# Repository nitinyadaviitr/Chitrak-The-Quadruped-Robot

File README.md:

MaRS_Kitty
Walking Quadruped Robot Kitty is a Quadruped that we are building under Models and Robotics Section, IIT Roorkee. 
This four legged walking robot will mimic the gait cycle of a cat with a soul purpose of providing help in natural calamities where 
normal robots find it difficult to move. 
Thank You.

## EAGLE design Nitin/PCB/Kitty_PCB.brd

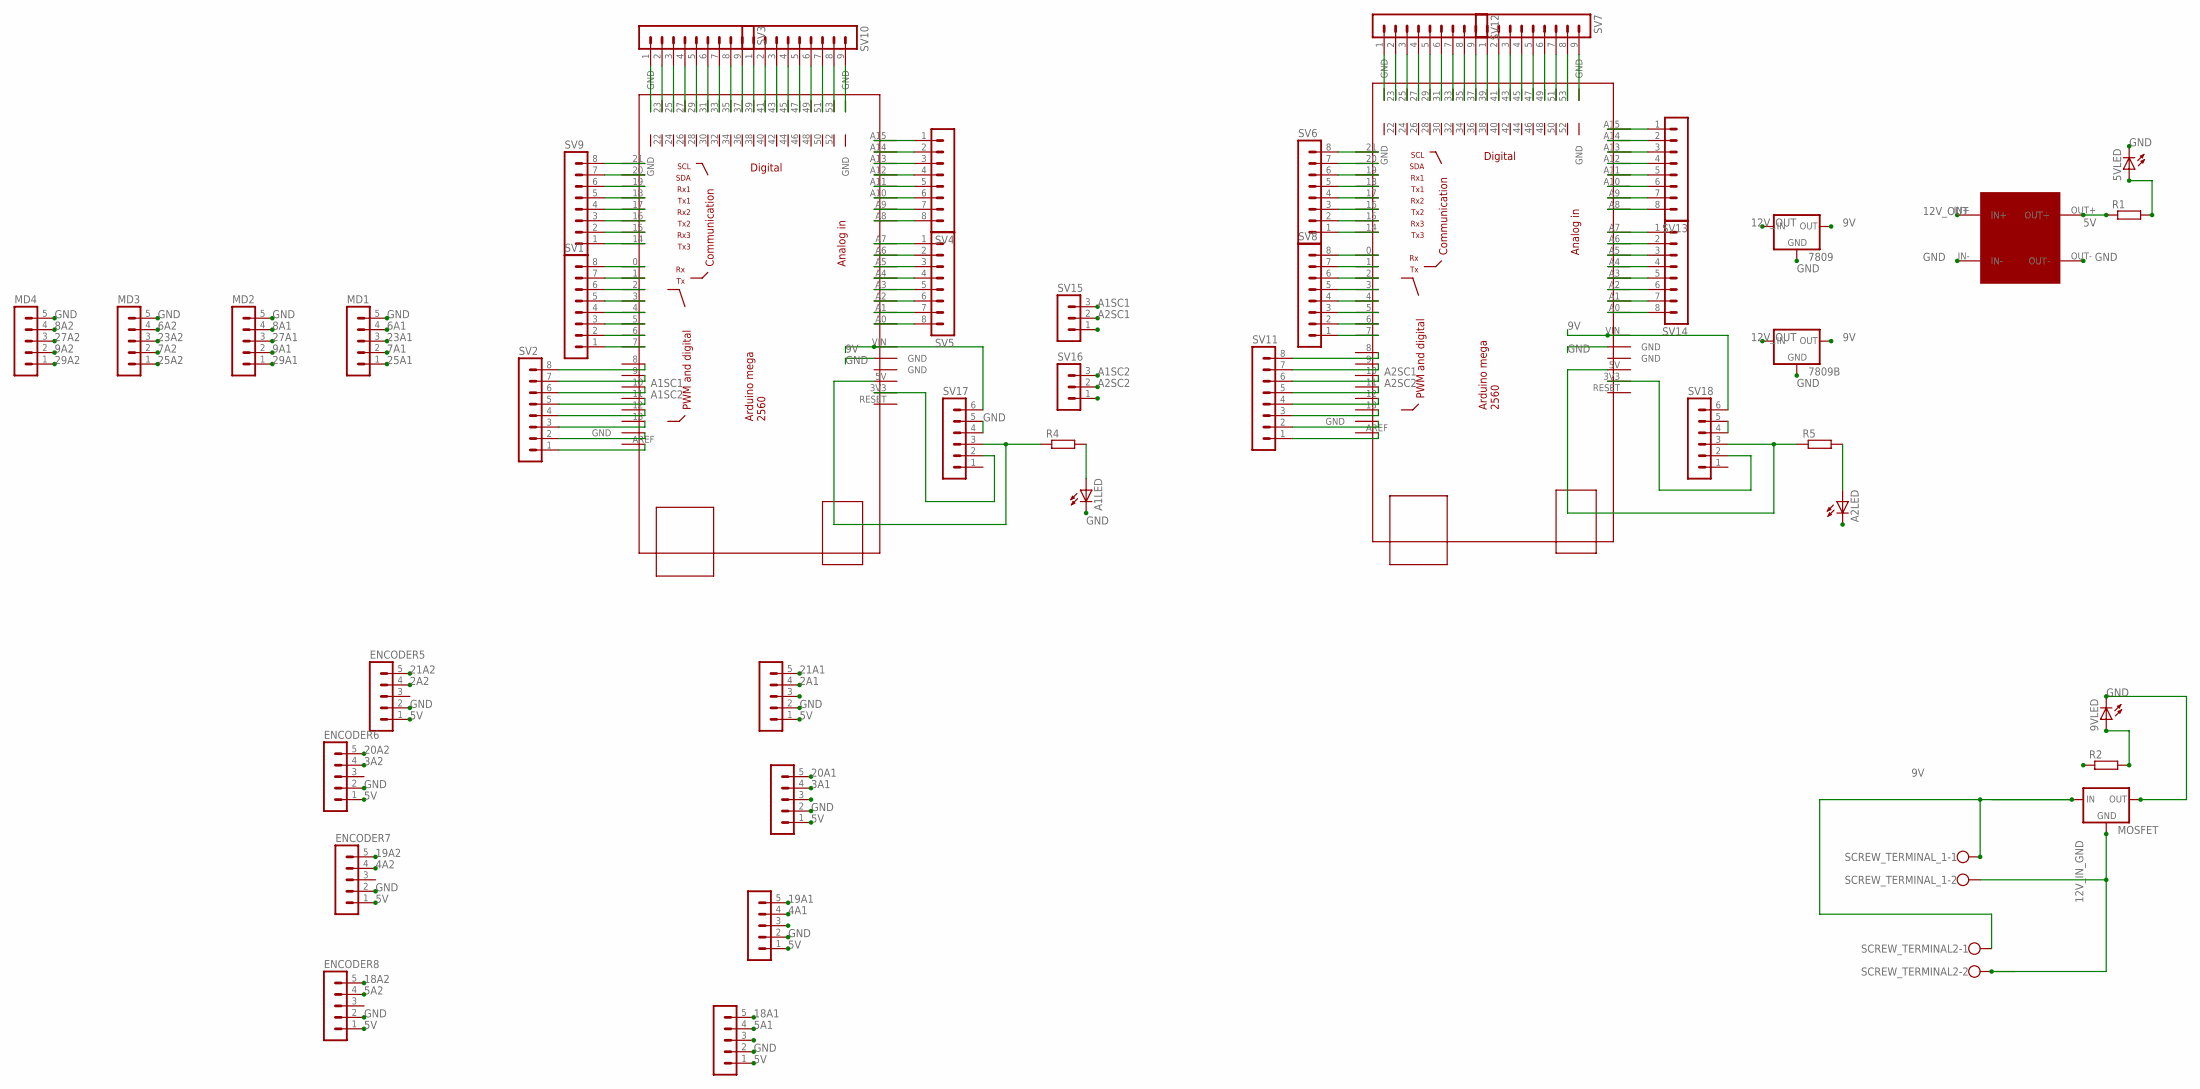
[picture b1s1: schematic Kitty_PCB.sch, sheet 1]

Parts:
5VLED, 9VLED: LED; LED3MM
7809, 7809B: VOLTAGE_REGULATOR_78XXS; 78XXS
A1LED, A2LED: LED; LED3MM
ARDUINO1, ARDUINO2: MEGA_DEVICE; MEGABOX
ENCODER1, ENCODER2, ENCODER3, ENCODER4, ENCODER5, ENCODER6, ENCODER7, ENCODER8: RELIMATE_05-1; MA05-1
MD1, MD2, MD3, MD4: RELIMATE_05-1; MA05-1
MOSFET: VOLTAGE_REGULATOR_78XXS; 78XXS
R1, R2, R4, R5: RESISTANCE0207/10; 0207/10
SCREW_TERMINAL2: SCREW_TERMINAL_POWER; POWER_CONNECTOR
SCREW_TERMINAL_1: SCREW_TERMINAL_POWER; POWER_CONNECTOR
SV1, SV2, SV4, SV5, SV6, SV8, SV9, SV11, SV13, SV14: RELIMATE_08-1; MA08-1
SV3, SV7, SV10, SV12: RELIMATE_09-1; MA09-1
SV15, SV16: RELIMATE_03-1; MA03-1
SV17, SV18: RELIMATE_06-1; MA06-1
U$1: BUCK_CONVERTER

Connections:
0A1: ARDUINO1.0, SV1.8
0A2: ARDUINO2.0, SV8.8
1A1: ARDUINO1.1, SV1.7
1A2: ARDUINO2.1, SV8.7
2A1: ARDUINO1.2, ENCODER1.4, SV1.6
2A2: ARDUINO2.2, ENCODER5.4, SV8.6
3A1: ARDUINO1.3, ENCODER2.4, SV1.5
3A2: ARDUINO2.3, ENCODER6.4, SV8.5
4A1: ARDUINO1.4, ENCODER3.4, SV1.4
4A2: ARDUINO2.4, ENCODER7.4, SV8.4
5A1: ARDUINO1.5, ENCODER4.4, SV1.3
5A2: ARDUINO2.5, ENCODER8.4, SV8.3
5V: ENCODER1.1, ENCODER2.1, ENCODER3.1, ENCODER4.1, ENCODER5.1, ENCODER6.1, ENCODER7.1, ENCODER8.1, R1.1, U$1.OUT+
6A1: ARDUINO1.6, MD1.4, SV1.2
6A2: ARDUINO2.6, MD3.4, SV8.2
7A1: ARDUINO1.7, MD1.2, SV1.1
7A2: ARDUINO2.7, MD3.2, SV8.1
8A1: ARDUINO1.8, MD2.4, SV2.8
8A2: ARDUINO2.8, MD4.4, SV11.8
9A1: MD2.2
9A2: ARDUINO1.9, ARDUINO2.9, MD4.2, SV2.7, SV11.7
9V: 7809.OUT, 7809B.OUT, ARDUINO1.VIN, ARDUINO2.VIN, R2.1, SV17.6, SV18.6
12A1: ARDUINO1.12, SV2.4
12A2: ARDUINO2.12, SV11.4
12V_IN_GND: MOSFET.GND, SCREW_TERMINAL2.2, SCREW_TERMINAL_1.2
12V_OUT: 7809.IN, 7809B.IN, MOSFET.IN, SCREW_TERMINAL2.1, SCREW_TERMINAL_1.1, U$1.IN+
13A1: ARDUINO1.13, SV2.3
13A2: ARDUINO2.13, SV11.3
14A1: ARDUINO1.14, SV9.1
14A2: ARDUINO2.14, SV6.1
15A1: ARDUINO1.15, SV9.2
15A2: ARDUINO2.15, SV6.2
16A1: ARDUINO1.16, SV9.3
16A2: ARDUINO2.16, SV6.3
17A1: ARDUINO1.17, SV9.4
17A2: ARDUINO2.17, SV6.4
18A1: ARDUINO1.18, ENCODER4.5, SV9.5
18A2: ARDUINO2.18, ENCODER8.5, SV6.5
19A1: ARDUINO1.19, ENCODER3.5, SV9.6
19A2: ARDUINO2.19, ENCODER7.5, SV6.6
20A1: ARDUINO1.20, ENCODER2.5, SV9.7
20A2: ARDUINO2.20, ENCODER6.5, SV6.7
21A1: ARDUINO1.21, ENCODER1.5, SV9.8
21A2: ARDUINO2.21, ENCODER5.5, SV6.8
23A1: ARDUINO1.23, MD1.3, SV3.2
23A2: ARDUINO2.23, MD3.3, SV12.2
25A1: ARDUINO1.25, MD1.1, SV3.3
25A2: ARDUINO2.25, MD3.1, SV12.3
27A1: ARDUINO1.27, MD2.3, SV3.4
27A2: ARDUINO2.27, MD4.3, SV12.4
29A1: ARDUINO1.29, MD2.1, SV3.5
29A2: ARDUINO2.29, MD4.1, SV12.5
31A1: ARDUINO1.31, SV3.6
31A2: ARDUINO2.31, SV12.6
33A1: ARDUINO1.33, SV3.7
33A2: ARDUINO2.33, SV12.7
35A1: ARDUINO1.35, SV3.8
35A2: ARDUINO2.35, SV12.8
37A1: ARDUINO1.37, SV3.9
37A2: ARDUINO2.37, SV12.9
A1SC1: ARDUINO1.10, SV2.6, SV15.3
A1SC2: ARDUINO1.11, SV2.5, SV16.3
A2SC1: ARDUINO2.10, SV11.6, SV15.2
A2SC2: ARDUINO2.11, SV11.5, SV16.2
GND: 5VLED.K (C), 9VLED.K (C), 7809.GND, 7809B.GND, A1LED.K (C), A2LED.K (C), ARDUINO1.GND@3 (GND), ARDUINO2.GND@3 (GND), ENCODER1.2, ENCODER2.2, ENCODER3.2, ENCODER4.2, ENCODER5.2, ENCODER6.2, ENCODER7.2, ENCODER8.2, MD1.5, MD2.5, MD3.5, MD4.5, MOSFET.OUT, SV17.4, SV17.5, U$1.IN-, U$1.OUT-
unnamed: ARDUINO1.3V3, SV17.2
unnamed: ARDUINO1.5V, R4.1, SV17.3
unnamed: 5VLED.A, R1.2
unnamed: SV18.4, SV18.5
unnamed: ARDUINO2.3V3, SV18.2
unnamed: ARDUINO2.5V, R5.1, SV18.3
unnamed: A1LED.A, R4.2
unnamed: A2LED.A, R5.2
unnamed: 9VLED.A, R2.2
unnamed: ARDUINO1.GND@5 (GND), SV3.1
unnamed: ARDUINO1.GND@1 (GND), SV2.2
unnamed: ARDUINO1.AREF, SV2.1
unnamed: ARDUINO1.A15, SV4.1
unnamed: ARDUINO1.A14, SV4.2
unnamed: ARDUINO1.A13, SV4.3
unnamed: ARDUINO1.A12, SV4.4
unnamed: ARDUINO1.A11, SV4.5
unnamed: ARDUINO1.A10, SV4.6
unnamed: ARDUINO1.A9, SV4.7
unnamed: ARDUINO1.A8, SV4.8
unnamed: ARDUINO1.A7, SV5.1
unnamed: ARDUINO1.A6, SV5.2
unnamed: ARDUINO1.A5, SV5.3
unnamed: ARDUINO1.A4, SV5.4
unnamed: ARDUINO1.A3, SV5.5
unnamed: ARDUINO1.A2, SV5.6
unnamed: ARDUINO1.A1, SV5.7
unnamed: ARDUINO1.A0, SV5.8
unnamed: ARDUINO2.GND@1 (GND), SV11.2
unnamed: ARDUINO2.AREF, SV11.1
unnamed: ARDUINO2.A15, SV13.1
unnamed: ARDUINO2.A14, SV13.2
unnamed: ARDUINO2.A13, SV13.3
unnamed: ARDUINO2.A12, SV13.4
unnamed: ARDUINO2.A11, SV13.5
unnamed: ARDUINO2.A10, SV13.6
unnamed: ARDUINO2.A9, SV13.7
unnamed: ARDUINO2.A8, SV13.8
unnamed: ARDUINO2.A7, SV14.1
unnamed: ARDUINO2.A6, SV14.2
unnamed: ARDUINO2.A5, SV14.3
unnamed: ARDUINO2.A4, SV14.4
unnamed: ARDUINO2.A3, SV14.5
unnamed: ARDUINO2.A2, SV14.6
unnamed: ARDUINO2.A1, SV14.7
unnamed: ARDUINO2.A0, SV14.8
unnamed: ARDUINO1.39, SV10.1
unnamed: ARDUINO1.41, SV10.2
unnamed: ARDUINO1.43, SV10.3
unnamed: ARDUINO1.45, SV10.4
unnamed: ARDUINO1.47, SV10.5
unnamed: ARDUINO1.49, SV10.6
unnamed: ARDUINO1.51, SV10.7
unnamed: ARDUINO1.53, SV10.8
unnamed: ARDUINO1.GND@7 (GND), SV10.9
unnamed: ARDUINO2.GND@5 (GND), SV12.1
unnamed: ARDUINO2.39, SV7.1
unnamed: ARDUINO2.41, SV7.2
unnamed: ARDUINO2.43, SV7.3
unnamed: ARDUINO2.45, SV7.4
unnamed: ARDUINO2.47, SV7.5
unnamed: ARDUINO2.49, SV7.6
unnamed: ARDUINO2.51, SV7.7
unnamed: ARDUINO2.53, SV7.8
unnamed: ARDUINO2.GND@7 (GND), SV7.9

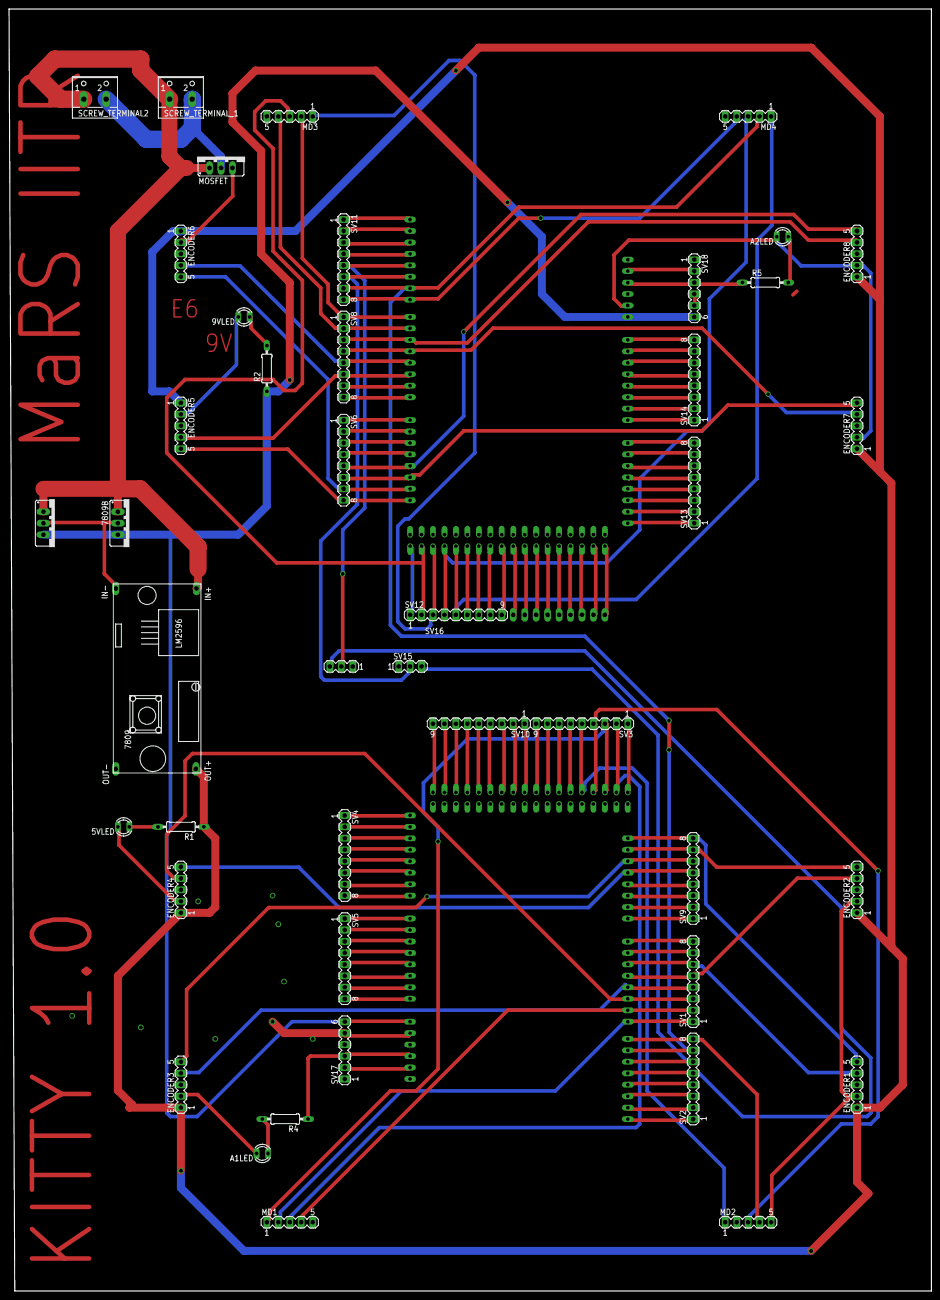
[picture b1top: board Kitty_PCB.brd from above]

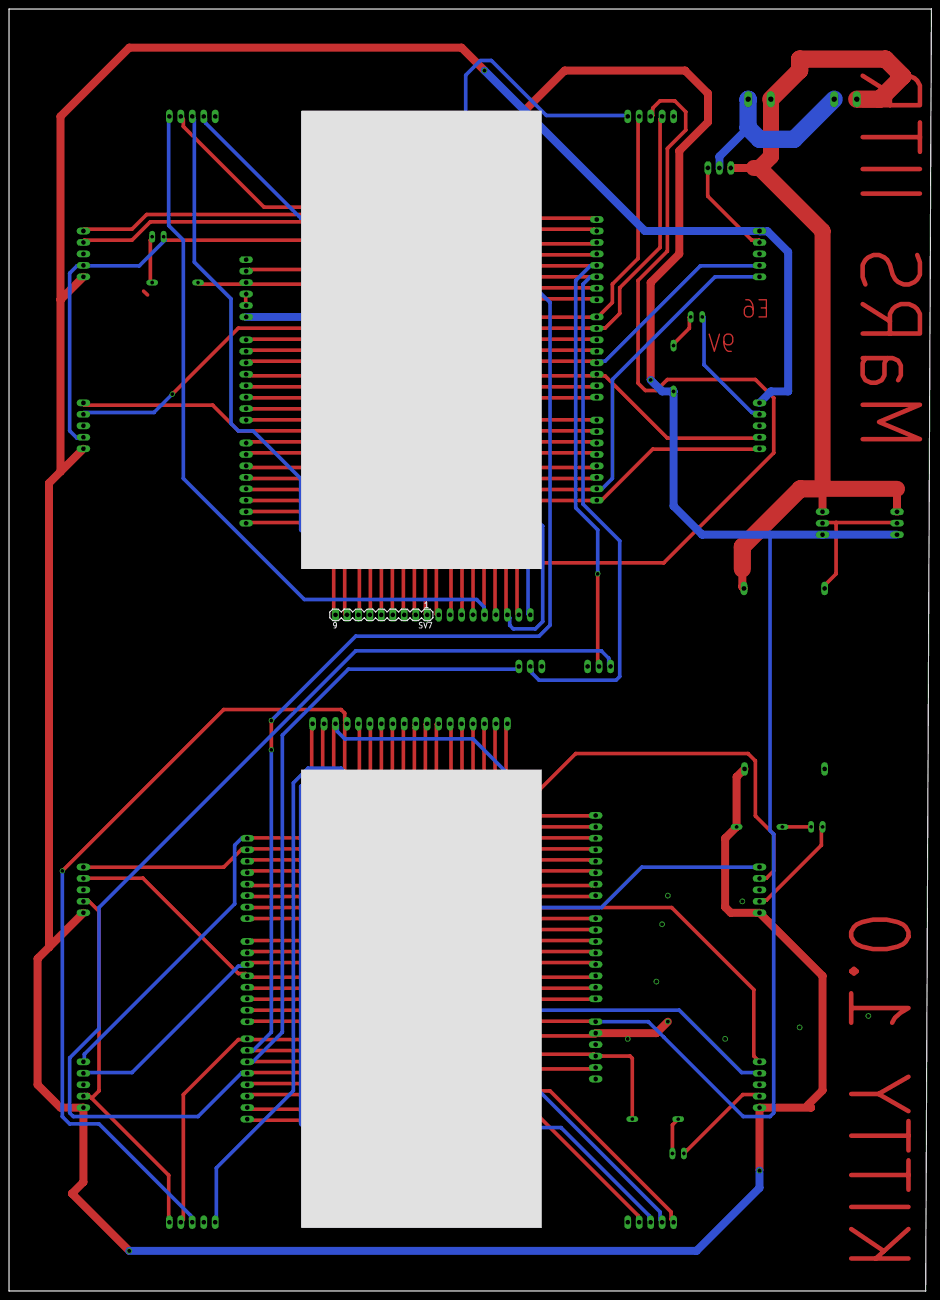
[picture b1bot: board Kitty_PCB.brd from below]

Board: 2 copper layers, 204.4 x 284.1 mm, 46 parts (3 on the bottom side), 129 nets.

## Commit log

2018-11-04 Quadruped Robot
    First Code Commit.
2018-11-04 Gait Correction
    Reduce the instant Jerk on 2 legs
2018-11-04 View Change
2018-11-05 Code with communication
    Individual arduino code done, master left.
2018-11-05 To change branch
2018-11-05 4 leg Code with communication, Master left.
2018-12-04 Pins updated
2018-12-05 Code for 4legs
    New changes made for smooth movement of four legs.
2018-12-05 updated till individual leg working
2018-12-07 updated final
2018-12-07 PCB
    PCB design for the bot
2018-12-10 PCB 1.0 Final
    1st version of the PCB is completed.
2018-12-11 New Things To be Added
    Integrating IMU for COM position
    Storing value in EEPROM of Arduino for repositioning off the bot each time it starts.
    Adding Spline to the motion of 1leg.
2018-12-13 PCB1 Final
    Final PCB for ettching completed.
2019-02-01 Change
